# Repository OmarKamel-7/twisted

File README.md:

# Twisted

Twisted is a tiny (14x32mm to be precise) ESP32-S3 based platform, which has dual Xtensa LX7 cores, 4Mb of flash, 2Mb of PSRAM, 512Kb of SRAM as well as BLE and WiFi on board, paired with an [0.42" IPS LCD](https://www.buydisplay.com/0-42-inch-mini-color-tft-lcd-display-module-96x54-ips-st7735), a keypad, a Neopixel and built-in battery management with USB OTG.

There is one more thing, the platform is extendable! It features a 20pin 1.27mm expansion header which allows you of attaching other boards that add more feature, and also give the _Twisted_ a reason for its name.

We currently have two expansion boards for Twisted...

- **Twisted Listen**: An audio codec based on ES8316, which provides a high performance DAC and ADC, the attachment comes with both a builtin microphone and amplifier for a loudspeaker, as well as a 3.5mm headphone jack (with microphone in.)

- **Twisted Sense (WIP)**: An attachment that provides a a suite of sensors and trackers (pressure, temperature, humidity, gyroscope, accelerometer, magnetometer and GPS/GNSS) aiming to help the device "feel" what happens surround it.

## Production

Production could be done through [JLCPCB](https://jlcpcb.com)'s PCBA service.

Total costs for Twisted boards:

| Item | Price | Qty      | Where                        |
| ---- | ----- | -------- | ---------------------------- |
| PCB  | $7    | 5 Boards | [JLCPCB](https://jlcpcb.com) |
| PCBA | $100  | 5 Boards | [JLCPCB](https://jlcpcb.com) |

You will need to assemble one side of the boardm the other side which has the display, a resistor and the keypad you will have to assemble it yourself, or let JLCPCB assemble it for you at a higher cost.

You will need the display to be sourced and assembled by yourself, this is where you can buy it:

- AliExpress: [listing](https://aliexpress.com/item/1005007804650049.html) / [listing](https://aliexpress.com/item/1005008528322628.html) / [listing](https://aliexpress.com/item/1005012246832580.html) / [listing](https://aliexpress.com/item/1005008885821582.html)
- [BuyDisplay](https://www.buydisplay.com/0-42-inch-mini-color-tft-lcd-display-module-96x54-ips-st7735)

If you decide to buy the display from a different supplier, make sure it comes with a 16 pin flex cable, it also has to follow this pinout:

Total costs for a Twisted Listen boards:

| Item | Price | Qty      | Where                        |
| ---- | ----- | -------- | ---------------------------- |
| PCB  | $7    | 5 Boards | [JLCPCB](https://jlcpcb.com) |
| PCBA | $60   | 5 Boards | [JLCPCB](https://jlcpcb.com) |

_Note that these tables don't include shipping charges._

Production files could be found in `/hardware/X/production`.

## GPIO Pins Mapping
| GPIO | Strap |    ADC   | HWSPI | Remark                                              |      Exposed      | On Twisted        |
|:----:|:-----:|:--------:|:-----:|-----------------------------------------------------|:-----------------:|-------------------|
|   0  |  Yes  |          |       | Pull LOW to Enter BOOT                              |         No        | Boot Button       |
|   1  |   No  | ADC1 CH0 |       |                                                     |        Yes        | Expansion Header  |
|   2  |   No  | ADC1 CH1 |       |                                                     |        Yes        | Expansion Header  |
|   3  |  Yes  | ADC1 CH2 |       | Pull LOW to Use An External Debugger Instead of USB |        Yes        | Expansion Header  |
|   4  |   No  | ADC1 CH3 |       |                                                     |        Yes        | Expansion Header  |
|   5  |   No  | ADC1 CH4 |       |                                                     |        Yes        | Expansion Header  |
|   6  |   No  | ADC1 CH5 |       |                                                     |        Yes        | Expansion Header  |
|   7  |   No  | ADC1 CH6 |       |                                                     |        Yes        | Expansion Header  |
|   8  |   No  | ADC1 CH7 |       |                                                     |        Yes        | Expansion Header  |
|   9  |   No  | ADC1 CH8 |  Hold |                                                     |        Yes        | Expansion Header  |
|  10  |   No  | ADC1 CH9 |   CS  |                                                     |        Yes        | Expansion Header  |
|  11  |   No  | ADC2 CH0 |  MOSI |                                                     |        Yes        | Expansion Header  |
|  12  |   No  | ADC2 CH1 |  SCK  |                                                     |        Yes        | Expansion Header  |
|  13  |   No  | ADC2 CH2 |  MISO |                                                     |        Yes        | Expansion Header  |
|  14  |   No  | ADC2 CH3 |   WP  |                                                     |        Yes        | Expansion Header  |
|  15  |   No  | ADC2 CH4 |       |                                                     |        Yes        | Expansion Header  |
|  16  |   No  | ADC2 CH5 |       |                                                     |        Yes        | Expansion Header  |
|  17  |   No  | ADC2 CH6 |       |                                                     |        Yes        | Expansion Header  |
|  18  |   No  | ADC2 CH7 |       |                                                     |         No        | Keypad: INT       |
|  19  |  Yes  | ADC2 CH8 |       | USB D-                                              |        Yes        | USB Port          |
|  20  |  Yes  | ADC2 CH9 |       | USB D+                                              |        Yes        | USB Port          |
|  21  |   No  |          |       |                                                     |         No        | Neopixel: DIN     |
|  26  |  Yes  |          |       | Used for QSPI Flash/PSRAM                           |         No        | Unused            |
|  27  |  Yes  |          |       | Used for QSPI Flash/PSRAM                           |         No        | Unused            |
|  28  |  Yes  |          |       | Used for QSPI Flash/PSRAM                           |         No        | Unused            |
|  29  |  Yes  |          |       | Used for QSPI Flash/PSRAM                           |         No        | Unused            |
|  30  |  Yes  |          |       | Used for QSPI Flash/PSRAM                           |         No        | Unused            |
|  31  |  Yes  |          |       | Used for QSPI Flash/PSRAM                           |         No        | Unused            |
|  32  |  Yes  |          |       | Used for QSPI Flash/PSRAM                           |         No        | Unused            |
|  33  | Maybe |          |       | Straps for Chips w/ Octal-SPI PSRAM                 |         No        | LCD: RST          |
|  34  | Maybe |          |       | Straps for Chips w/ Octal-SPI PSRAM                 |         No        | LCD: SCK          |
|  35  | Maybe |          |       | Straps for Chips w/ Octal-SPI PSRAM                 |         No        | LCD: CS           |
|  36  | Maybe |          |       | Straps for Chips w/ Octal-SPI PSRAM                 |         No        | LCD: MOSI         |
|  37  | Maybe |          |       | Straps for Chips w/ Octal-SPI PSRAM                 |         No        | LCD: BKL          |
|  38  |   No  |          |       |                                                     |         No        | Unused            |
|  39  |   No  |          |       |                                                     |         No        | Keypad: RST       |
|  40  |   No  |          |       |                                                     |         No        | Unused            |
|  41  |   No  |          |       |                                                     | Through Testpoint | Internal I2C: SDA |
|  42  |   No  |          |       |                                                     | Through Testpoint | Internal I2C: SDA |
|  43  |   No  |          |       | Default UART: TX                                    | Through Testpoint | Unused            |
|  44  |   No  |          |       | Default UART: RX                                    | Through Testpoint | Unused            |
|  45  |  Yes  |          |       |                                                     |         No        | Unused            |
|  46  |  Yes  |          |       |                                                     |         No        | Unused            |
|  47  |   No  |          |       |                                                     |         No        | LCD: DC           |
|  48  |   No  |          |       |                                                     |         No        | BMS: INT          |

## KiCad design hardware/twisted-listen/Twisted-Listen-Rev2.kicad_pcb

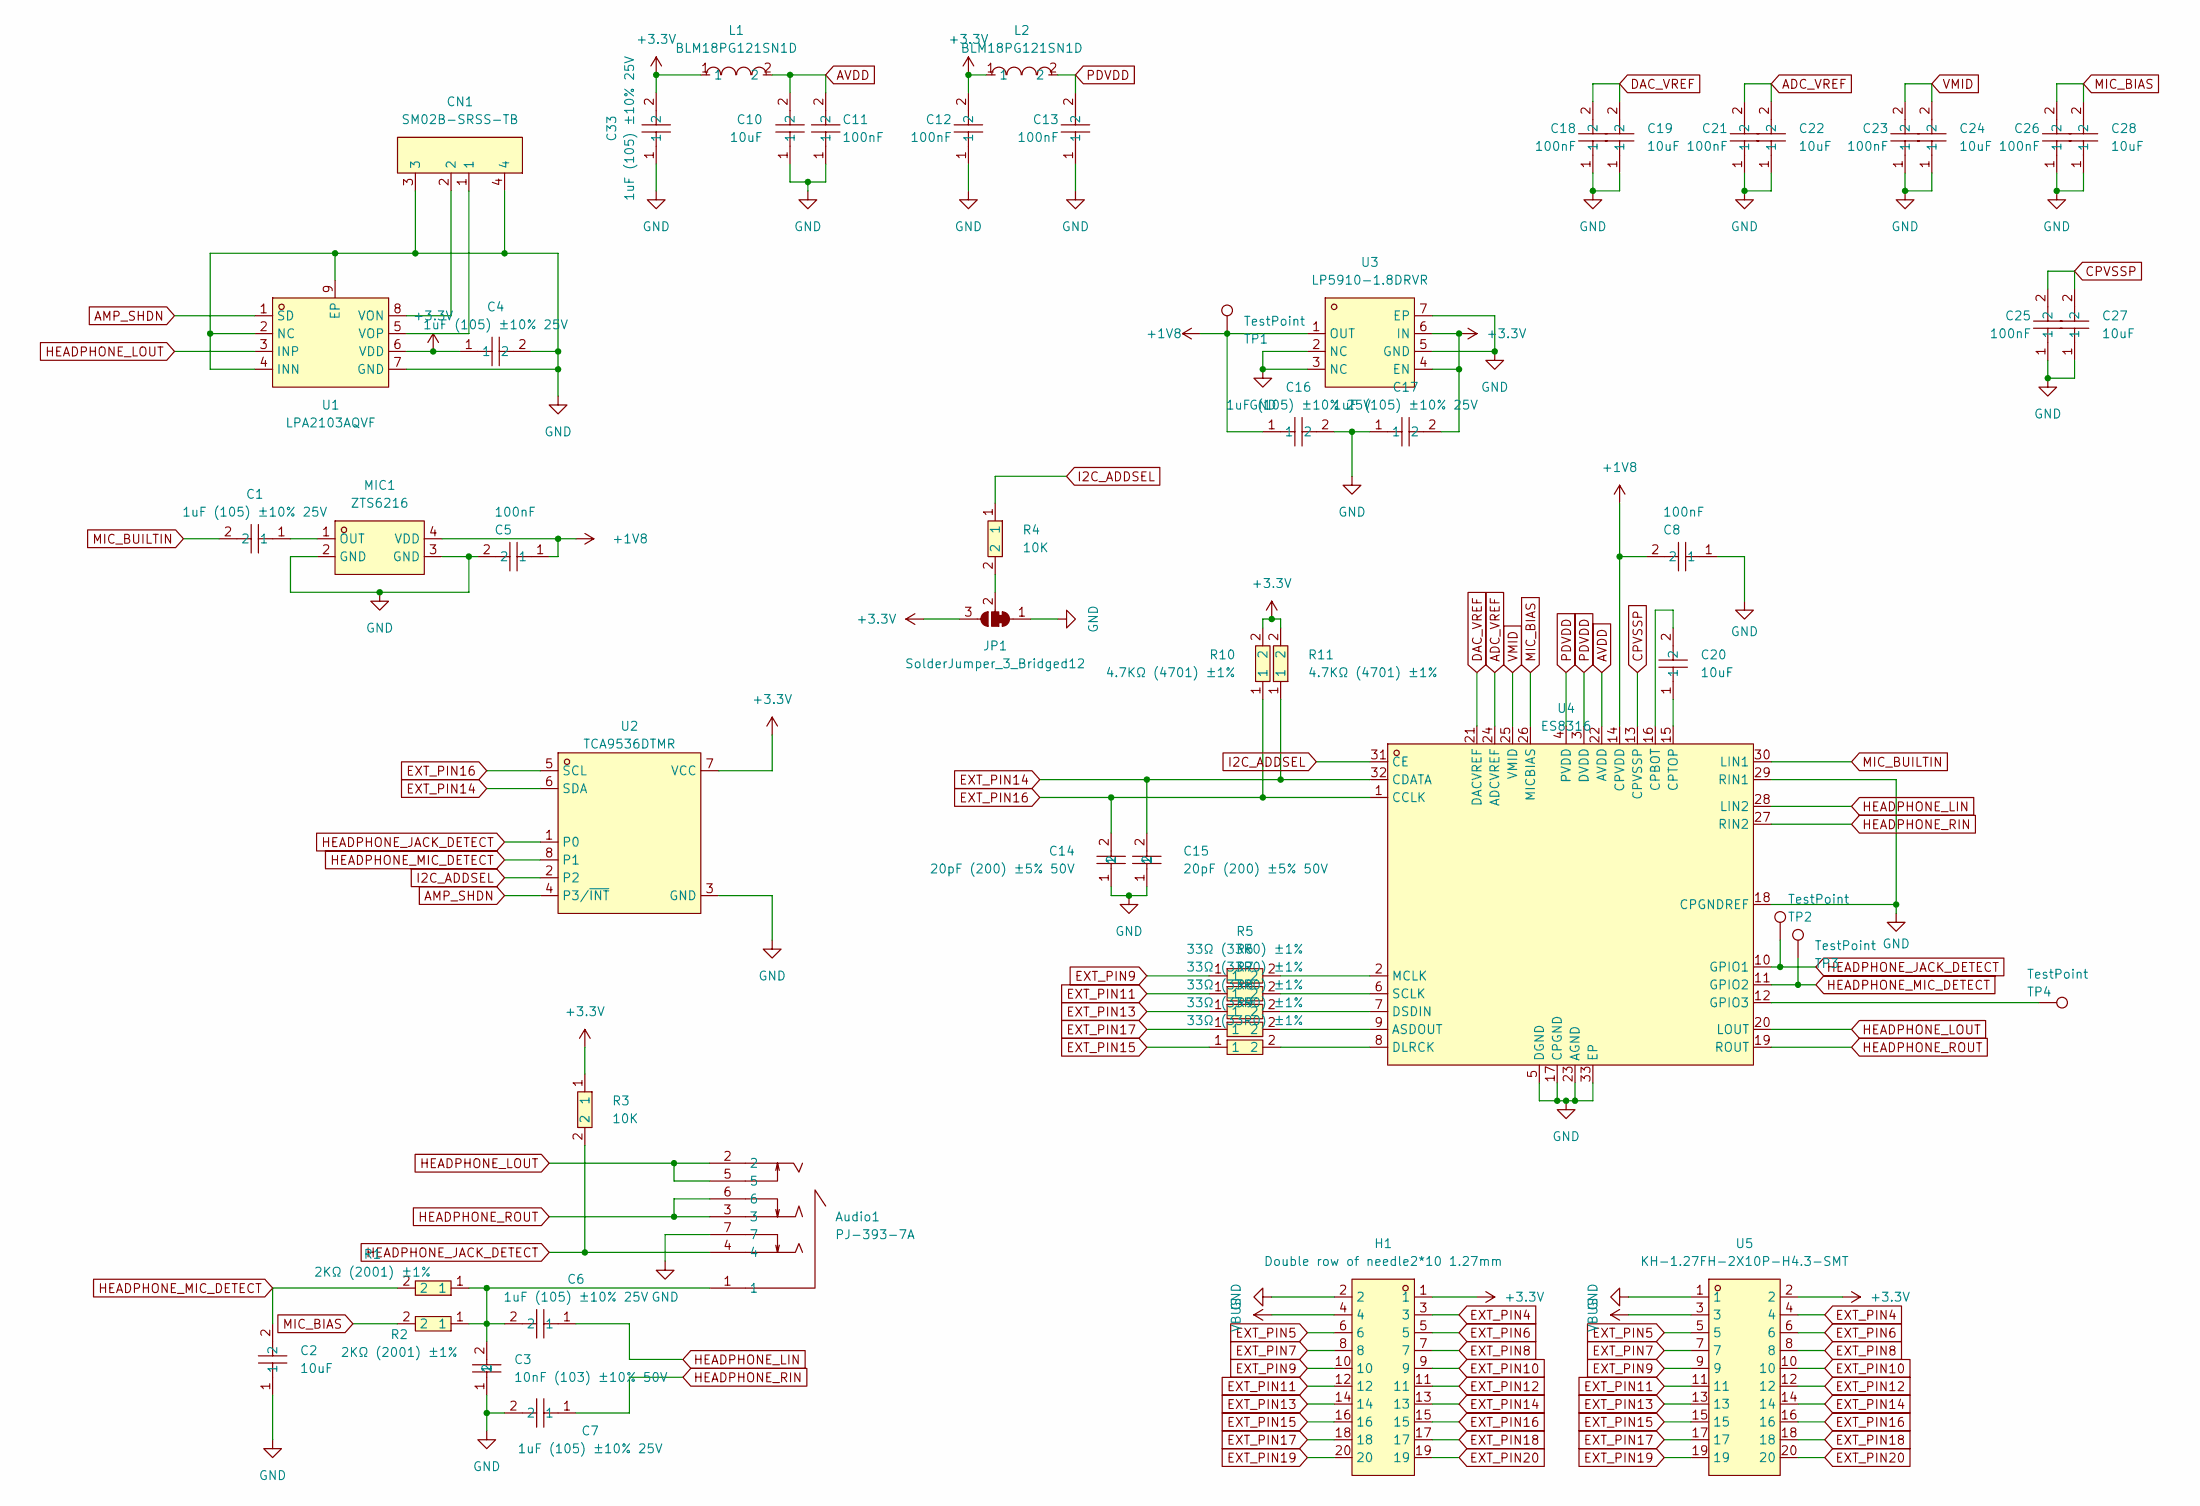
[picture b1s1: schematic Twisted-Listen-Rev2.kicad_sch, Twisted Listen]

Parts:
Audio1: PJ-393-7A; AUDIO-SMD_PJ-393-7A; MPN PJ-393-7A; LCSC Part C128990
C1, C4, C6, C7, C16, C17, C33: CL05A105KA5NQNC; C0402; MPN CL05A105KA5NQNC; LCSC Part C52923
C2, C10, C19, C20, C22, C24, C27, C28: CL05A106MP5NUNC_C315248; C0402; LCSC Part C315248
C3: CL05B103KB5NNNC; C0402; MPN CL05B103KB5NNNC; LCSC Part C15195
C5, C8, C11, C12, C13, C18, C21, C23, C25, C26: CC0402KRX7R7BB104; C0402; LCSC Part C60474
C14, C15: 0402CG200J500NT; C0402; MPN 0402CG200J500NT; LCSC Part C1554
CN1: SM02B-SRSS-TB; CONN-SMD_2P-P1.00_SM02B-SRSS-TB-LF-SN; MPN SM02B-SRSS-TB(LF)(SN); LCSC Part C160402
H1: Double row of needle2*10 1.27mm; HDR-SMD_20P-P1.27-V-M-R2-C10-S1.27-LS5.5-1; MPN 1.27-2*10P立贴针; LCSC Part C59981
JP1: SolderJumper_3_Bridged12; SolderJumper-3_P1.3mm_Bridged12_RoundedPad1.0x1.5mm
L1, L2: BLM18PG121SN1D; L0603; MPN BLM18PG121SN1D; LCSC Part C14709
MIC1: ZTS6216; MIC-SMD_4P-L2.8-W1.9-P1.84-TL; MPN ZTS6216; LCSC Part C481302
R1, R2: 0402WGF2001TCE; R0402; MPN 0402WGF2001TCE; LCSC Part C4109
R3, R4: 0402WGF1002TCE; R0402; LCSC Part C25744
R5, R6, R7, R8, R9: 0402WGF330JTCE; R0402; MPN 0402WGF330JTCE; LCSC Part C25105
R10, R11: 0402WGF4701TCE; R0402; MPN 0402WGF4701TCE; LCSC Part C25900
TP1, TP2, TP3, TP4: TestPoint; TinyTestPoint
U1: LPA2103AQVF; DFN-8_L2.0-W2.0-P0.50-BL-EP1.5; MPN LPA2103AQVF; LCSC Part C42460075
U2: TCA9536DTMR; X2SON-8_L1.4-W0.8-P0.50-BL; MPN TCA9536DTMR; LCSC Part C3190167
U3: LP5910-1.8DRVR; WSON-6_L2.0-W2.0-P0.65-TL-EP; MPN LP5910-1.8DRVR; LCSC Part C2867568
U4: ES8316; QFN-32_L4.0-W4.0-P0.40-BL-EP2.7; MPN ES8316; LCSC Part C365735
U5: KH-1.27FH-2X10P-H4.3-SMT; CONN-SMD_20P-P1.27_KINGHELM_KH-1.27FH-2X10P-H4.3-SMT; LCSC Part C2938399

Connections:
+1V8: C5.1, C8.2, C16.1, MIC1.4 (VDD), TP1.1, U3.1 (OUT), U4.14 (CPVDD)
+3.3V: C4.1, C12.2, C17.2, C33.2, H1.1, JP1.3 (B), L1.1, L2.1, R3.1, R10.2, R11.2, U1.6 (VDD), U2.7 (VCC), U3.4 (EN), U3.6 (IN), U5.2
ADC_VREF: C21.2, C22.2, U4.24 (ADCVREF)
AMP_SHDN: U1.1 (SD), U2.4 (P3/~INT)
AVDD: C10.2, C11.2, L1.2, U4.22 (AVDD)
CPVSSP: C25.2, C27.2, U4.13 (CPVSSP)
DAC_VREF: C18.2, C19.2, U4.21 (DACVREF)
EXT_PIN4: H1.3, U5.4
EXT_PIN5: H1.6, U5.5
EXT_PIN6: H1.5, U5.6
EXT_PIN7: H1.8, U5.7
EXT_PIN8: H1.7, U5.8
EXT_PIN9: H1.10, R5.1, U5.9
EXT_PIN10: H1.9, U5.10
EXT_PIN11: H1.12, R6.1, U5.11
EXT_PIN12: H1.11, U5.12
EXT_PIN13: H1.14, R7.1, U5.13
EXT_PIN14: C15.2, H1.13, R11.1, U2.6 (SDA), U4.32 (CDATA), U5.14
EXT_PIN15: H1.16, R9.1, U5.15
EXT_PIN16: C14.2, H1.15, R10.1, U2.5 (SCL), U4.1 (CCLK), U5.16
EXT_PIN17: H1.18, R8.1, U5.17
EXT_PIN18: H1.17, U5.18
EXT_PIN19: H1.20, U5.19
EXT_PIN20: H1.19, U5.20
GND: Audio1.7, C2.1, C3.1, C4.2, C5.2, C7.2, C8.1, C10.1, C11.1, C12.1, C13.1, C14.1, C15.1, C16.2, C17.1, C18.1, C19.1, C21.1, C22.1, C23.1, C24.1, C25.1, C26.1, C27.1, C28.1, C33.1, CN1.3, CN1.4, H1.2, JP1.1 (A), MIC1.2 (GND), MIC1.3 (GND), U1.2 (NC), U1.4 (INN), U1.7 (GND), U1.9 (EP), U2.3 (GND), U3.2 (NC), U3.3 (NC), U3.5 (GND), U3.7 (EP), U4.5 (DGND), U4.17 (CPGND), U4.18 (CPGNDREF), U4.23 (AGND), U4.29 (RIN1), U4.33 (EP), U5.1
HEADPHONE_JACK_DETECT: Audio1.4, R3.2, TP2.1, U2.1 (P0), U4.10 (GPIO1)
HEADPHONE_LIN: C6.1, U4.28 (LIN2)
HEADPHONE_LOUT: Audio1.2, Audio1.5, U1.3 (INP), U4.20 (LOUT)
HEADPHONE_MIC_DETECT: C2.2, R1.2, TP3.1, U2.8 (P1), U4.11 (GPIO2)
HEADPHONE_RIN: C7.1, U4.27 (RIN2)
HEADPHONE_ROUT: Audio1.3, Audio1.6, U4.19 (ROUT)
I2C_ADDSEL: R4.1, U2.2, U4.31 (CE)
MIC_BIAS: C26.2, C28.2, R2.2, U4.26 (MICBIAS)
MIC_BUILTIN: C1.2, U4.30 (LIN1)
unnamed: Audio1.1, C3.2, C6.2, R1.1, R2.1
unnamed: JP1.2 (C), R4.2
unnamed: C1.1, MIC1.1 (OUT)
unnamed: CN1.2, U1.8 (VON)
unnamed: CN1.1, U1.5 (VOP)
unnamed: R8.2, U4.9 (ASDOUT)
unnamed: C20.2, U4.16 (CPBOT)
unnamed: C20.1, U4.15 (CPTOP)
unnamed: R9.2, U4.8 (DLRCK)
unnamed: R7.2, U4.7 (DSDIN)
unnamed: TP4.1, U4.12 (GPIO3)
unnamed: R5.2, U4.2 (MCLK)
unnamed: R6.2, U4.6 (SCLK)
PDVDD: C13.2, L2.2, U4.3 (DVDD), U4.4 (PVDD)
VBUS: H1.4, U5.3
VMID: C23.2, C24.2, U4.25 (VMID)

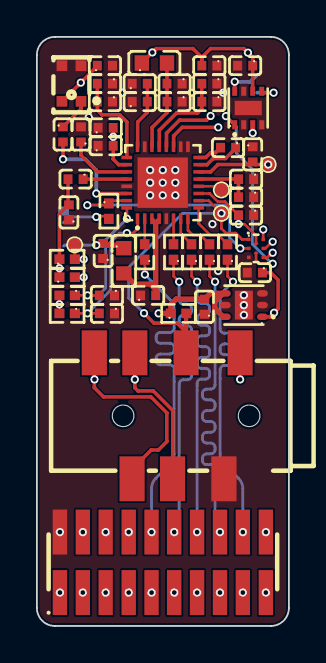
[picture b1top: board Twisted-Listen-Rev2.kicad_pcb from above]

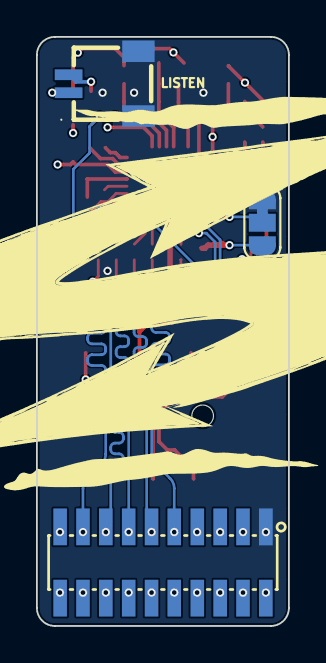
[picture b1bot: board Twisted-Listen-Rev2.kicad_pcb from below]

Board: 4 copper layers, 14.0 x 32.7 mm, 55 parts (3 on the bottom side), 50 nets.

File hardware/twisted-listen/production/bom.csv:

Designator,Footprint,Quantity,Value,LCSC Part #
AUDIO1,AUDIO-SMD_PJ-393-7A,1,PJ-393-7A,C128990
"C1, C16, C17, C33, C4, C6, C7",C0402,7,CL05A105KA5NQNC,C52923
"C10, C19, C2, C20, C22, C24, C27, C28",C0402,8,CL05A106MP5NUNC_C315248,C315248
"C11, C12, C13, C18, C21, C23, C25, C26, C5, C8",C0402,10,CC0402KRX7R7BB104,C60474
"C14, C15",C0402,2,0402CG200J500NT,C1554
C3,C0402,1,CL05B103KB5NNNC,C15195
CN1,CONN-SMD_2P-P1.00_SM02B-SRSS-TB-LF-SN,1,SM02B-SRSS-TB,C160402
H1,HDR-SMD_20P-P1.27-V-M-R2-C10-S1.27-LS5.5-1,1,Double row of needle2*10 1.27mm,C59981
"L1, L2",L0603,2,BLM18PG121SN1D,C14709
MIC1,MIC-SMD_4P-L2.8-W1.9-P1.84-TL,1,ZTS6216,C481302
"R1, R2",R0402,2,0402WGF2001TCE,C4109
"R10, R11",R0402,2,0402WGF4701TCE,C25900
"R3, R4",R0402,2,0402WGF1002TCE,C25744
"R5, R6, R7, R8, R9",R0402,5,0402WGF330JTCE,C25105
"TP1, TP2, TP3, TP4",TinyTestPoint,4,TestPoint,
U1,DFN-8_L2.0-W2.0-P0.50-BL-EP1.5,1,LPA2103AQVF,C42460075
U2,X2SON-8_L1.4-W0.8-P0.50-BL,1,TCA9536DTMR,C3190167
U3,WSON-6_L2.0-W2.0-P0.65-TL-EP,1,LP5910-1.8DRVR,C2867568
U4,QFN-32_L4.0-W4.0-P0.40-BL-EP2.7,1,ES8316,C365735
U5,CONN-SMD_20P-P1.27_KINGHELM_KH-1.27FH-2X10P-H4.3-SMT,1,KH-1.27FH-2X10P-H4.3-SMT,C2938399

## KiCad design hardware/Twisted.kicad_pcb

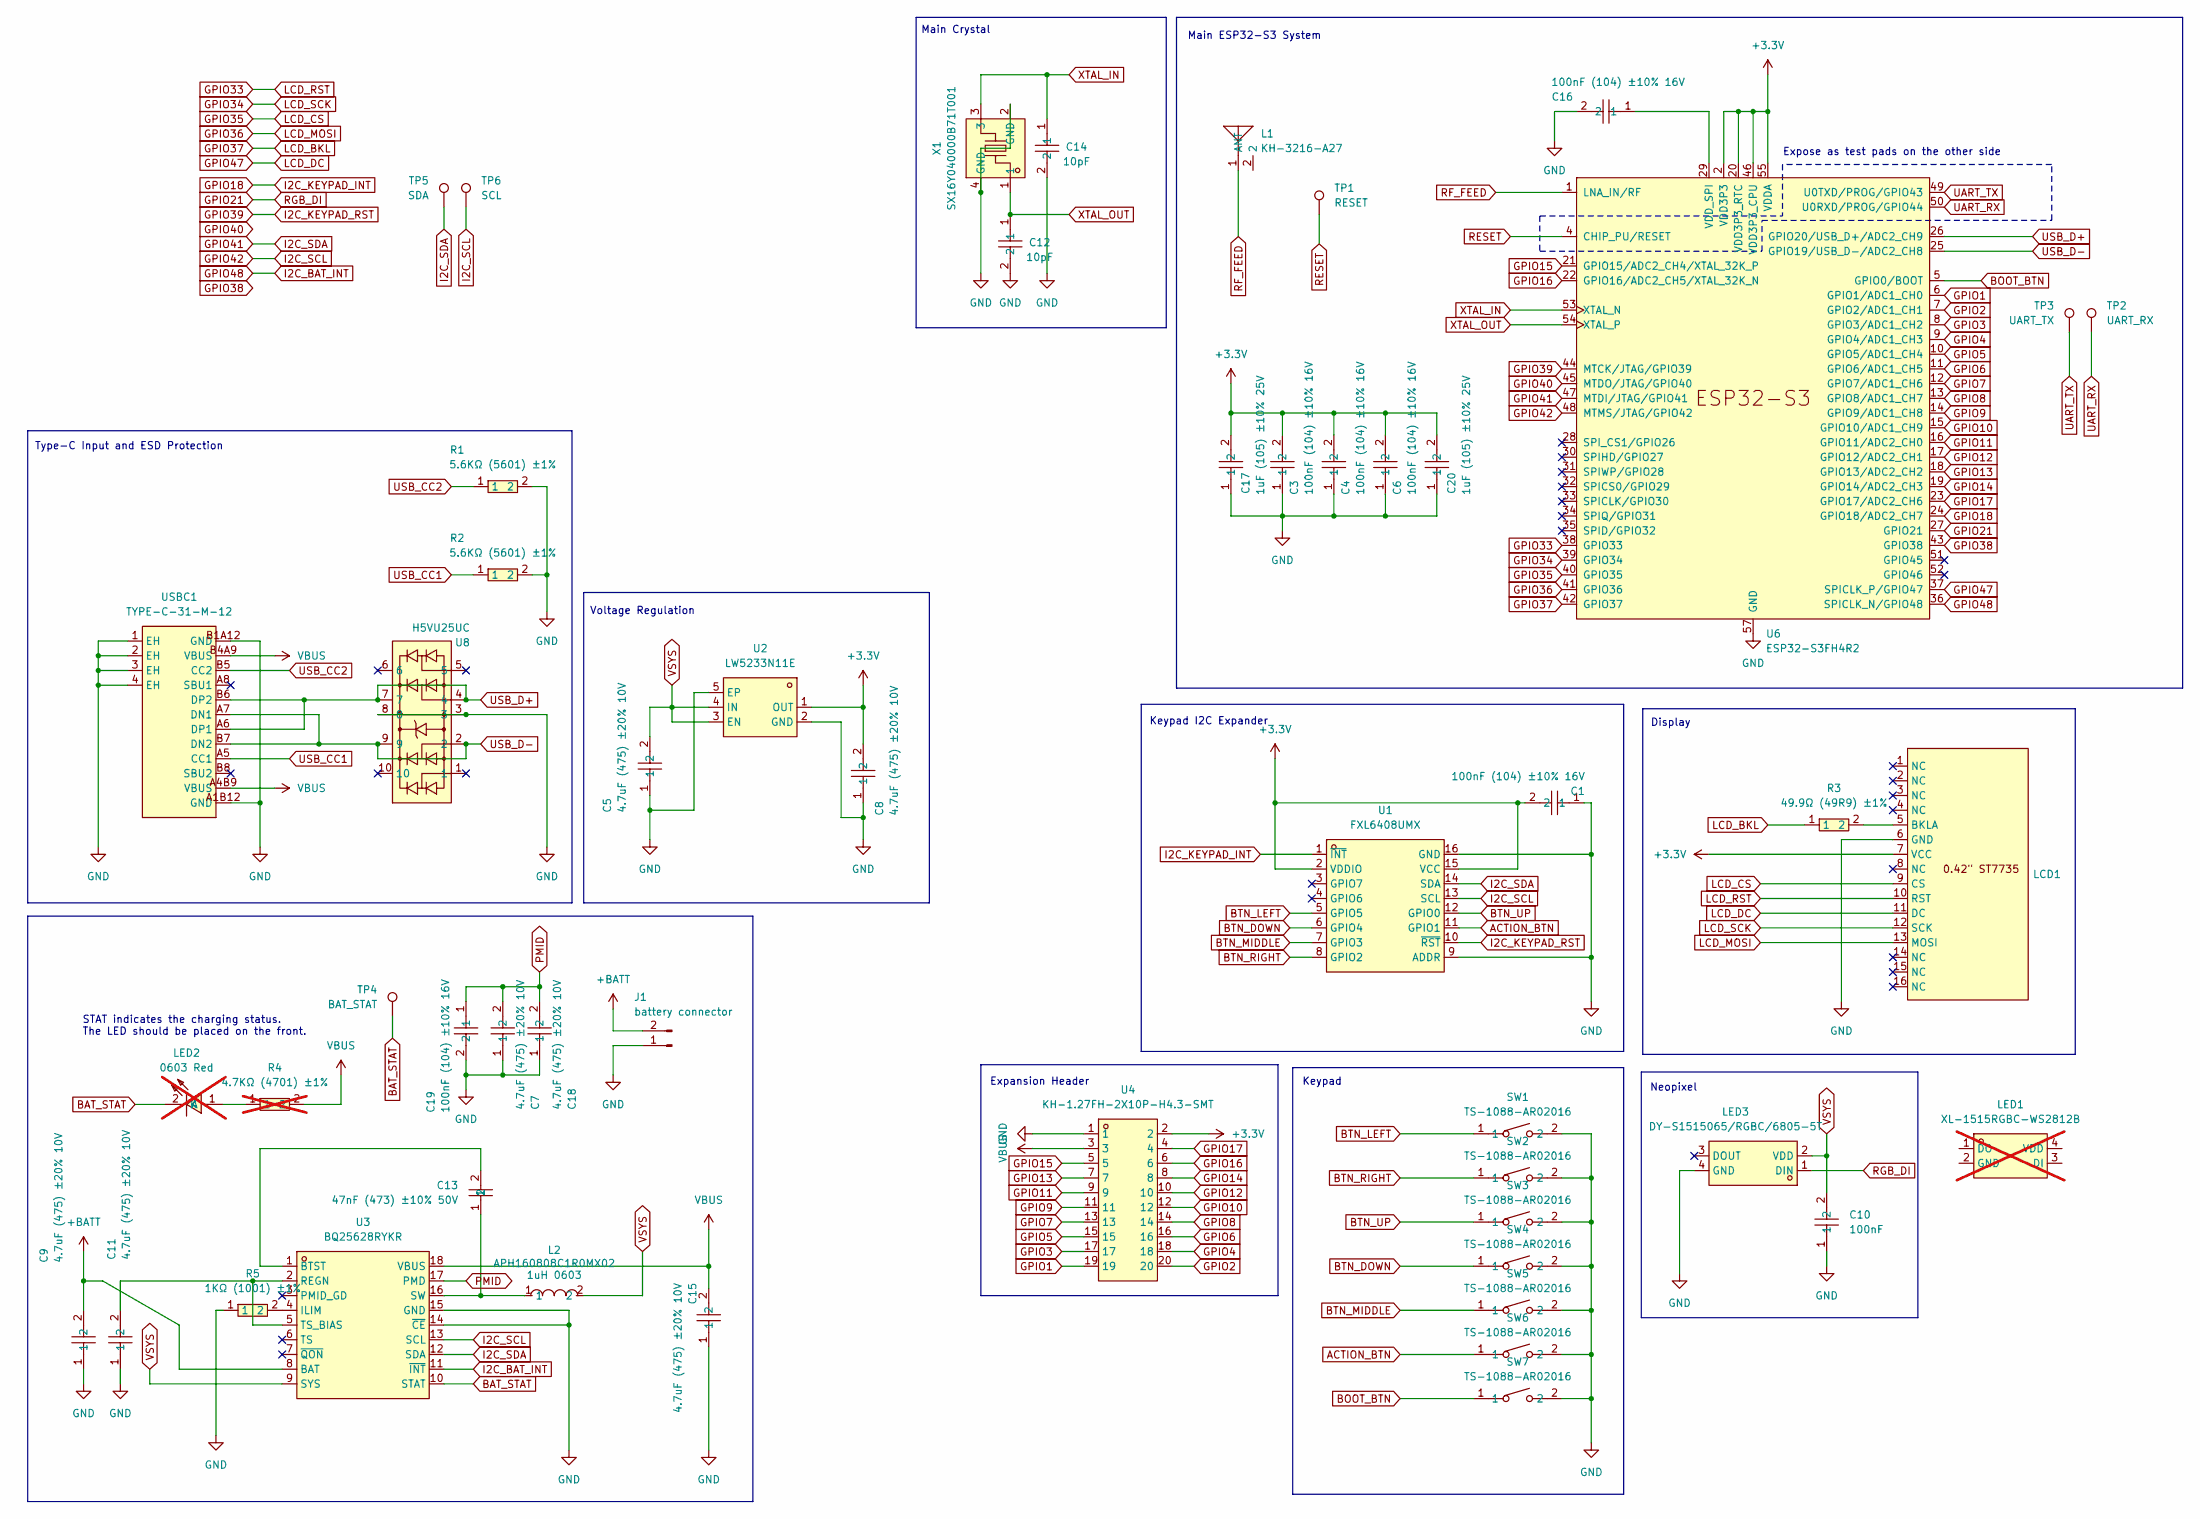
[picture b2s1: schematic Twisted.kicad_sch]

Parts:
C1, C3, C4, C6, C16, C19: CL05B104KO5NNNC; C0402; MPN CL05B104KO5NNNC; LCSC Part C1525
C5, C7, C8, C9, C11, C15, C18: CL05A475MP5NRNC; C0402; MPN CL05A475MP5NRNC; LCSC Part C23733
C10: CC0402KRX7R7BB104; C0402; LCSC Part C60474
C12, C14: CL05C100JB5NNNC; C0402; LCSC Part C32949
C13: CL10B473KB8NNNC; C0603; MPN CL10B473KB8NNNC; LCSC Part C1622
C17, C20: CL05A105KA5NQNC; C0402; MPN CL05A105KA5NQNC; LCSC Part C52923
J1: battery connector; PinSocket_1x02_P1.27mm_Vertical
L1: KH-3216-A27; ANT-SMD_L3.2-W1.6; MPN KH-3216-A27; LCSC Part C504001
L2: APH160808C1R0MX02; L0603; MPN APH160808C1R0MP01; LCSC Part C54123751
LCD1: 0.42-ST7735-Bent
LED1: XL-1515RGBC-WS2812B; LED-ARRAY-SMD_4P-L1.6-W1.5-P0.85-TL; MPN XL-1515RGBC-2812B; LCSC Part C48586673; not fitted
LED2: KT-0603R; LED-SMD_L1.6-W0.8-R-RD; MPN KT-0603R; LCSC Part C2286; not fitted
LED3: DY-S1515065/RGBC/6805-5T; LED-SMD_4P-L1.5-W1.5; MPN DY-S1515065/RGBC/6805-5T; LCSC Part C524053
R1, R2: 0402WGF5601TCE; R0402; MPN 0402WGF5601TCE; LCSC Part C25908
R3: 0402WGF499JTCE; R0402; MPN 0402WGF499JTCE; LCSC Part C25120
R4: 0402WGF4701TCE; R0402; MPN 0402WGF4701TCE; LCSC Part C25900; not fitted
R5: 0402WGF1001TCE; R0402; MPN 0402WGF1001TCE; LCSC Part C11702
SW1, SW2, SW3, SW4, SW5, SW6, SW7: TS-1088-AR02016; SW-SMD_L3.9-W3.0-P4.45; LCSC Part C720477
TP1: RESET; 2xTinyTestPoint
TP2: UART_RX; 2xTinyTestPoint
TP3: UART_TX; 2xTinyTestPoint
TP4: BAT_STAT; TinyTestPoint
TP5: SDA; TinyTestPoint
TP6: SCL; TinyTestPoint
U1: FXL6408UMX; UQFN-16_L2.6-W1.8-P0.40-BL; MPN FXL6408UMX; LCSC Part C457770
U2: LW5233N11E; DFN-4_L1.0-W1.0-P0.65-BL-EP; MPN LW5233N11E; LCSC Part C20630430
U3: BQ25628RYKR; WQFN-18_L3.0-W2.5-P0.40-TL; MPN BQ25628RYKR; LCSC Part C6055599
U4: KH-1.27FH-2X10P-H4.3-SMT; CONN-SMD_20P-P1.27_KINGHELM_KH-1.27FH-2X10P-H4.3-SMT; LCSC Part C2938399
U6: ESP32-S3FH4R2; QFN-56_L7.0-W7.0-P0.40-BL-EP5.7; LCSC Part C3013940
U8: H5VU25UC; DFN2510-10_L2.5-W1.0-P0.50-BL; MPN H5VU25UC; LCSC Part C20615800
USBC1: TYPE-C-31-M-12; USB-C_SMD-TYPE-C-31-M-12_1; LCSC Part C165948
X1: SX16Y040000B71T001; CRYSTAL-SMD_4P-L1.6-W1.2-BL; LCSC Part C20623634

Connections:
+BATT: C9.2, J1.2, U3.8 (BAT)
ACTION_BTN: SW6.1, U1.11 (GPIO1)
BAT_STAT: LED2.2 (K), TP4.1 (1_1), U3.10 (STAT)
BOOT_BTN: SW7.1, U6.5 (GPIO0/BOOT)
BTN_DOWN: SW4.1, U1.6 (GPIO4)
BTN_LEFT: SW1.1, U1.5 (GPIO5)
BTN_MIDDLE: SW5.1, U1.7 (GPIO3)
BTN_RIGHT: SW2.1, U1.8 (GPIO2)
BTN_UP: SW3.1, U1.12 (GPIO0)
GND: C1.1, C3.1, C4.1, C5.1, C6.1, C7.1, C8.1, C9.1, C10.1, C11.1, C12.2, C14.2, C15.1, C16.2, C17.1, C18.1, C19.2, C20.1, J1.1, LCD1.6 (GND), LED3.4 (GND), R1.2, R2.2, R5.1, SW1.2, SW2.2, SW3.2, SW4.2, SW5.2, SW6.2, SW7.2, U1.9 (ADDR), U1.16 (GND), U2.2 (GND), U2.5 (EP), U3.14 (~CE), U3.15 (GND), U4.1, U6.57 (GND), U8.3, U8.8, USBC1.1 (EH), USBC1.2 (EH), USBC1.3 (EH), USBC1.4 (EH), USBC1.A1B12 (GND), USBC1.B1A12 (GND), X1.2 (GND), X1.4 (GND); also elsewhere on the board
GPIO1: U4.19, U6.6 (GPIO1/ADC1_CH0)
GPIO2: U4.20, U6.7 (GPIO2/ADC1_CH1)
GPIO3: U4.17, U6.8 (GPIO3/ADC1_CH2)
GPIO4: U4.18, U6.9 (GPIO4/ADC1_CH3)
GPIO5: U4.15, U6.10 (GPIO5/ADC1_CH4)
GPIO6: U4.16, U6.11 (GPIO6/ADC1_CH5)
GPIO7: U4.13, U6.12 (GPIO7/ADC1_CH6)
GPIO8: U4.14, U6.13 (GPIO8/ADC1_CH7)
GPIO9: U4.11, U6.14 (GPIO9/ADC1_CH8)
GPIO10: U4.12, U6.15 (GPIO10/ADC1_CH9)
GPIO11: U4.9, U6.16 (GPIO11/ADC2_CH0)
GPIO12: U4.10, U6.17 (GPIO12/ADC2_CH1)
GPIO13: U4.7, U6.18 (GPIO13/ADC2_CH2)
GPIO14: U4.8, U6.19 (GPIO14/ADC2_CH3)
GPIO15: U4.5, U6.21 (GPIO15/ADC2_CH4/XTAL_32K_P)
GPIO16: U4.6, U6.22 (GPIO16/ADC2_CH5/XTAL_32K_N)
GPIO17: U4.4, U6.23 (GPIO17/ADC2_CH6)
GPIO18: U1.1 (~INT), U6.24 (GPIO18/ADC2_CH7)
GPIO21: LED3.1 (DIN), U6.27 (GPIO21)
GPIO33: LCD1.10 (RST), U6.38 (GPIO33)
GPIO34: LCD1.12 (SCK), U6.39 (GPIO34)
GPIO35: LCD1.9 (CS), U6.40 (GPIO35)
GPIO36: LCD1.13 (MOSI), U6.41 (GPIO36)
GPIO37: R3.1, U6.42 (GPIO37)
GPIO38: U6.43 (GPIO38)
GPIO39: U1.10 (~RST), U6.44 (MTCK/JTAG/GPIO39)
GPIO40: U6.45 (MTDO/JTAG/GPIO40)
GPIO41: TP5.1 (1_1), U1.14 (SDA), U3.12 (SDA), U6.47 (MTDI/JTAG/GPIO41)
GPIO42: TP6.1 (1_1), U1.13 (SCL), U3.13 (SCL), U6.48 (MTMS/JTAG/GPIO42)
GPIO47: LCD1.11 (DC), U6.37 (SPICLK_P/GPIO47)
GPIO48: U3.11 (~INT), U6.36 (SPICLK_N/GPIO48)
unnamed: LCD1.5 (BKLA), R3.2
unnamed: LED2.1 (A), R4.1
unnamed: C13.2, U3.1 (BTST)
unnamed: R5.2, U3.4 (ILIM)
unnamed: C11.2, U3.2 (REGN), U3.5 (TS_BIAS)
unnamed: C13.1, L2.1, U3.16 (SW)
unnamed: C16.1, U6.29 (VDD_SPI)
PMID: C7.2, C18.2, C19.1, U3.17 (PMD)
RESET: TP1.1 (1_1), U6.4 (CHIP_PU/RESET)
RF_FEED: L1.1 (ANT_1), U6.1 (LNA_IN/RF)
UART_RX: TP2.1 (1_1), U6.50 (U0RXD/PROG/GPIO44)
UART_TX: TP3.1 (1_1), U6.49 (U0TXD/PROG/GPIO43)
USB_CC1: R2.1, USBC1.A5 (CC1)
USB_CC2: R1.1, USBC1.B5 (CC2)
USB_D+: U6.26 (GPIO20/USB_D+/ADC2_CH9), U8.4, U8.7, USBC1.A6 (DP1), USBC1.B6 (DP2)
USB_D-: U6.25 (GPIO19/USB_D-/ADC2_CH8), U8.2, U8.9, USBC1.A7 (DN1), USBC1.B7 (DN2)
VBUS: C15.2, R4.2, U3.18 (VBUS), U4.3, USBC1.A4B9 (VBUS), USBC1.B4A9 (VBUS)
XTAL_IN: C14.1, U6.53 (XTAL_N), X1.3
XTAL_OUT: C12.1, U6.54 (XTAL_P), X1.1

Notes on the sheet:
Main ESP32-S3 System
Expose as test pads on the other side
Neopixel
Keypad I2C Expander
STAT indicates the charging status. The LED should be placed on the front.
Type-C Input and ESD Protection
Main Crystal
Display
Expansion Header
Keypad
Voltage Regulation

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
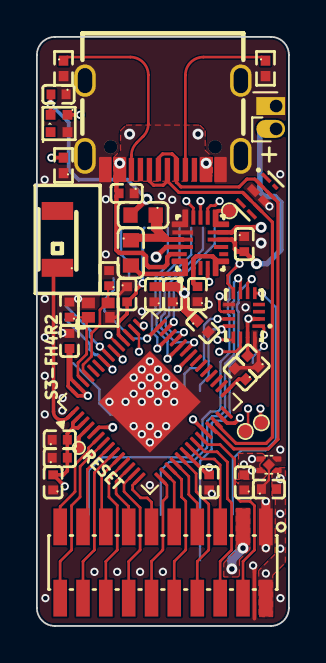
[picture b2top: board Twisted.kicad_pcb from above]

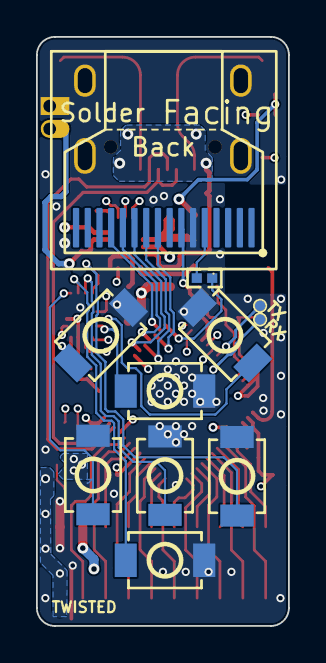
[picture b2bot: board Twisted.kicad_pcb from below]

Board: 4 copper layers, 14.0 x 32.7 mm, 50 parts (11 on the bottom side), 59 nets.

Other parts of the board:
C10#2: CC0402KRX7R7BB104; C0402

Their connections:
GND: C10#2.1; also elsewhere on the board
